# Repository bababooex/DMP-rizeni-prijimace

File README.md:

# DMP-rizeni-prijimace
Program a schémata mé maturitní praktické práce. Některé návrhy DPS, popřípadě části programu se dají použít pro jiné účely. Vše slouží pro inspiraci a nemůžu nic garantovat. Knihovny by měly být použitelné i s jinými projekty s STM8S208RB a kompilátorem COSMIC.
# Co všechno program obsahuje?
- Kompletní knihovna na řízení digitálního potenciometru od Adafruitu - DS1841
- Kompletní knihovna na řízení kanálového voliče FM1216 (čip TSA5523)
- Kompletní knihovna na řízení kanálového modulátoru RMUP74055 (čip MBS74T1AEF)
- Kompletní knihovna na řízení satelitního kanálového voliče s čipem AV2026 (v mém programu nepoužito)
- Kompletní knihovna na řízení modulu hodin reálného času s čipem PCF8563
- Knihovna pro maticovou klávesnici s neblokujícím časovým ošetřením stisku
- Upravená knihovna pro 4x40 lcd display se dvěma jednotkami HD44780 (případně ekvivalenty)
- Knihovna pro zobrazení velkého fontu (dvouřádkového) pro lcd display (jenom čísla)
- Knihovna pro řízení rotačních enkodérů softwarově

A další spousta podpůrných knihoven určených specificky pro tento projekt (práce s pamětí, pásmo, vlastní znaky, přepínání režimů...) a samozřejmě hlavní program main
# Co je v KiCadu
- Úplné schéma zapojení hlavní DPS s tlačítkovou DPS, vlastní footprinty a kompletní návrhy obou DPS
# Vzhled
Vzhled sestaveného zařízení

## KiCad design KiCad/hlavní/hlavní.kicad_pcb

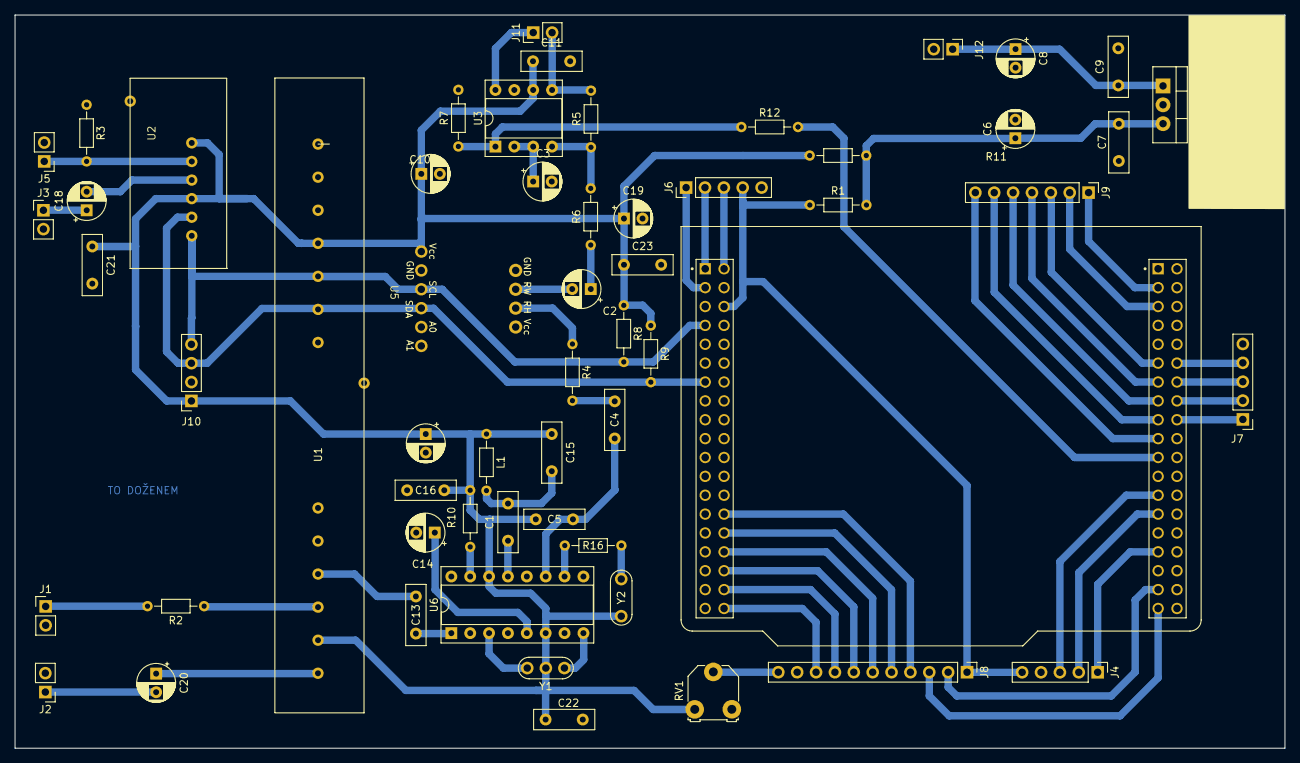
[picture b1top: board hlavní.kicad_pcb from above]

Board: 2 copper layers, 170.9 x 98.7 mm, 58 parts (0 on the bottom side), 61 nets.

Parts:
C1: 15pF; C_Disc_D8.0mm_W2.5mm_P5.00mm
C2, C3, C10: 1uF; CP_Radial_D5.0mm_P2.50mm
C4, C7, C9, C11, C16, C21, C22, C23: 100nF; C_Disc_D8.0mm_W2.5mm_P5.00mm
C5: 10nF; C_Disc_D8.0mm_W2.5mm_P5.00mm
C6, C17: 100uF; CP_Radial_D5.0mm_P2.50mm
C8: 470uF; CP_Radial_D5.0mm_P2.50mm
C13: 1nF; C_Disc_D8.0mm_W2.5mm_P5.00mm
C14, C18, C20: 10uF; CP_Radial_D5.0mm_P2.50mm
C15: 20pF; C_Disc_D8.0mm_W2.5mm_P5.00mm
C19: 220uF; CP_Radial_D5.0mm_P2.50mm
J1: VIDEO OUT; PinHeader_1x02_P2.54mm_Vertical
J2: AUDIO OUT; PinHeader_1x02_P2.54mm_Vertical
J3: AUDIO IN; PinHeader_1x02_P2.54mm_Vertical
J4: Tuning; PinHeader_1x05_P2.54mm_Vertical
J5: VIDEO IN; PinHeader_1x02_P2.54mm_Vertical
J6: Volume; PinHeader_1x05_P2.54mm_Vertical
J7: Buttons; PinHeader_1x05_P2.54mm_Vertical
J8: LCD Display; PinHeader_1x11_P2.54mm_Vertical
J9: Matrix keypad; PinHeader_1x07_P2.54mm_Vertical
J10: RTC CLOCK; PinSocket_1x04_P2.54mm_Vertical
J11: FM OUT; PinHeader_1x02_P2.54mm_Vertical
J12: DC IN; PinHeader_1x02_P2.54mm_Vertical
L1: 2.2uH; R_Axial_DIN0204_L3.6mm_D1.6mm_P7.62mm_Horizontal
R1, R11: 0Ω; R_Axial_DIN0204_L3.6mm_D1.6mm_P7.62mm_Horizontal
R2, R16: 100Ω; R_Axial_DIN0204_L3.6mm_D1.6mm_P7.62mm_Horizontal
R3: 75Ω; R_Axial_DIN0204_L3.6mm_D1.6mm_P7.62mm_Horizontal
R4: 47kΩ; R_Axial_DIN0204_L3.6mm_D1.6mm_P7.62mm_Horizontal
R5: 27kΩ; R_Axial_DIN0204_L3.6mm_D1.6mm_P7.62mm_Horizontal
R6: 10kΩ; R_Axial_DIN0204_L3.6mm_D1.6mm_P7.62mm_Horizontal
R7: 100kΩ; R_Axial_DIN0204_L3.6mm_D1.6mm_P7.62mm_Horizontal
R8, R9: 2.2kΩ; R_Axial_DIN0204_L3.6mm_D1.6mm_P7.62mm_Horizontal
R10: 1kΩ; R_Axial_DIN0204_L3.6mm_D1.6mm_P7.62mm_Horizontal
R12: 330Ω; R_Axial_DIN0204_L3.6mm_D1.6mm_P7.62mm_Horizontal
RV1: 5kΩ; TRIMPOT_ROUND
U1: TSA5523
U2: MBS74T1AEF
U3: 8002; DIP-8_W7.62mm_Socket
U4: STM8S208-NUCLEO; ST_NUCLEO-F303RE
U5: ds1841
U6: CD2003GB_GP; DIP-16_W7.62mm_Socket
U7: L7805; LM7805
Y1: 10.7MHz; Resonator-3Pin_W7.0mm_H2.5mm
Y2: 10.7MHz; Resonator-2Pin_W7.0mm_H2.5mm

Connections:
GND: C3.2, C6.2, C7.2, C8.2, C9.2, C10.2, C11.2, C14.2, C16.2, C17.2, C19.2, C21.2, C22.2, C23.2, J1.2, J2.2, J3.2, J4.4, J5.2, J6.5, J7.5, J8.10, J10.2, J12.2, R3.1, R7.2, RV1.1, U1.14 (GND), U2.7 (GND), U3.7 (GND), U4.5 (NC), U4.6 (NC), U4.10 (GND), U4.11 (NC), U4.28 (GND), U4.29 (GND), U4.34 (NC), U4.35 (GND), U4.43 (GND), U4.67 (GND), U5.1 (GND), U6.2 (GND_IN), U6.9 (GND_OUT), U7.2 (GND)
unnamed: C1.2, C15.2, L1.2
unnamed: C2.1, R6.1
unnamed: C4.2, R4.2
unnamed: J1.1, R2.2
unnamed: C20.2, J2.1
unnamed: C18.1, J3.1
unnamed: J4.1, U4.54 (PC1)
unnamed: J4.2, U4.52 (PC2)
unnamed: J4.3, U4.51 (PC3)
unnamed: J4.5, J6.4, J8.1, R1.1, U4.36 (E5V)
unnamed: J5.1, R3.2, U2.2 (VID)
unnamed: J6.1, U4.2 (PG5)
unnamed: J6.2, U4.1 (PG4)
unnamed: J6.3, U4.38 (PG7)
unnamed: J7.1, U4.68 (PF3)
unnamed: J7.2, U4.69 (PF4)
unnamed: J7.3, U4.70 (PF5)
unnamed: J7.4, U4.71 (PF6)
unnamed: J8.2, U4.56 (PD5)
unnamed: J8.3, U4.57 (PD6)
unnamed: J8.4, U4.25 (PB5)
unnamed: J8.5, U4.24 (PB4)
unnamed: J8.6, U4.23 (PB3)
unnamed: J8.7, U4.22 (PB2)
unnamed: J8.8, U4.21 (PB1)
unnamed: J8.9, U4.20 (PB0)
unnamed: J8.11, RV1.2
unnamed: J9.1, U4.40 (PE1)
unnamed: J9.2, U4.41 (PE2)
unnamed: J9.3, U4.44 (PC5)
unnamed: J9.4, U4.45 (PC7)
unnamed: J9.5, U4.46 (PC6)
unnamed: J9.6, U4.47 (PE5)
unnamed: J9.7, U4.48 (PC4)
unnamed: C5.2, C10.1, C11.1, C15.1, C16.1, C17.1, C19.1, C21.1, C22.1, C23.1, J10.1, L1.1, R8.1, R9.1, R10.2, R11.1, RV1.3, U1.4 (+BT), U1.12 (+BD), U2.1 (BB), U2.4 (MB), U3.6 (VDD), U5.4 (Vcc), U6.6 (VCC), U6.14 (FM/AM_SW), Y1.2, Y2.1
unnamed: J10.3, R9.2, U1.6 (SDA), U2.5 (SDA), U4.7 (PE6), U5.8 (SDA)
unnamed: J10.4, R8.2, U1.5 (SCL), U2.6 (SCL), U4.4 (PE7), U5.7 (SCL)
unnamed: J11.1, U3.8 (V02)
unnamed: J11.2, R5.2, U3.5 (V01)
unnamed: C8.1, C9.1, J12.1, U7.1 (IN)
unnamed: R16.1, Y2.2
unnamed: C20.1, U1.13 (AF)
unnamed: R2.1, U1.11 (CVBS)
unnamed: C13.2, U1.10 (MPX)
unnamed: C18.2, U2.3 (AUD)
unnamed: C3.1, U3.2 (BYP), U3.3 (+IN)
unnamed: R5.1, R6.2, U3.4 (-IN)
unnamed: R7.1, R12.1, U3.1 (SD)
unnamed: R12.2, U4.49 (PD3)
unnamed: R4.1, U5.3 (RH)
unnamed: C2.2, U5.2 (RW)
unnamed: C14.1, U6.5 (AGC)
unnamed: C4.1, C5.1, U6.11 (DET_OUT)
unnamed: R16.2, U6.10 (FM_DET)
unnamed: U6.8 (FM_IF), Y1.1
unnamed: U6.3 (FM_MIX), Y1.3
unnamed: C1.1, U6.13 (FM_OSC)
unnamed: C13.1, U6.1 (FM_RF_IN)
unnamed: R10.1, U6.15 (FM_TUNER)
unnamed: C6.1, C7.1, R1.2, R11.2, U7.3 (OUT)

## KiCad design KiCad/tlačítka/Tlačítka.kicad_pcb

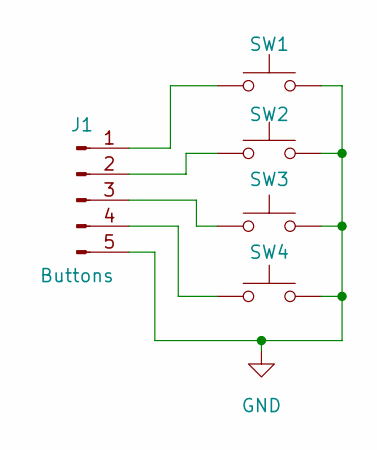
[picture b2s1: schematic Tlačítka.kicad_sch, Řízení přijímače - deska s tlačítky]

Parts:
J1: Buttons; PinSocket_1x05_P2.54mm_Vertical
SW1, SW2, SW3, SW4: SW_Push; SW_PUSH-12mm

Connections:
GND: J1.5, SW1.2, SW2.2, SW3.2, SW4.2
unnamed: J1.1, SW1.1
unnamed: J1.2, SW2.1
unnamed: J1.3, SW3.1
unnamed: J1.4, SW4.1

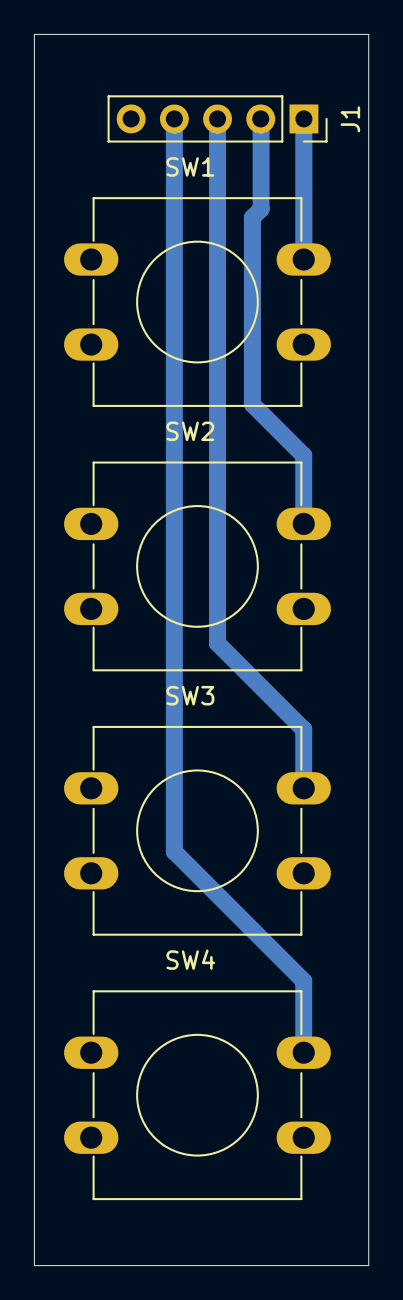
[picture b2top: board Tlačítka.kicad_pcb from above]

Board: 2 copper layers, 19.7 x 72.4 mm, 5 parts (0 on the bottom side), 5 nets.

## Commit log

2026-04-28 Enhance README with program details and libraries
    Updated README to provide detailed information about the program, including libraries and KiCad schematics.
